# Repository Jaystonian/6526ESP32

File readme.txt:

6526ESP32

v0.1 - Largely disabled wifi, device boots into Ready mode instead of Modem mode
     - Added 1541diag (to use, poke 56704,5:poke 56705,0:sys56777)
     - Intended to use a new version of BASIC with new commands to use the
     device easily without pokes or sys calls, and also replace math etc.

v0.0 - straight conversion from ESP8266, added a few things but very dirty

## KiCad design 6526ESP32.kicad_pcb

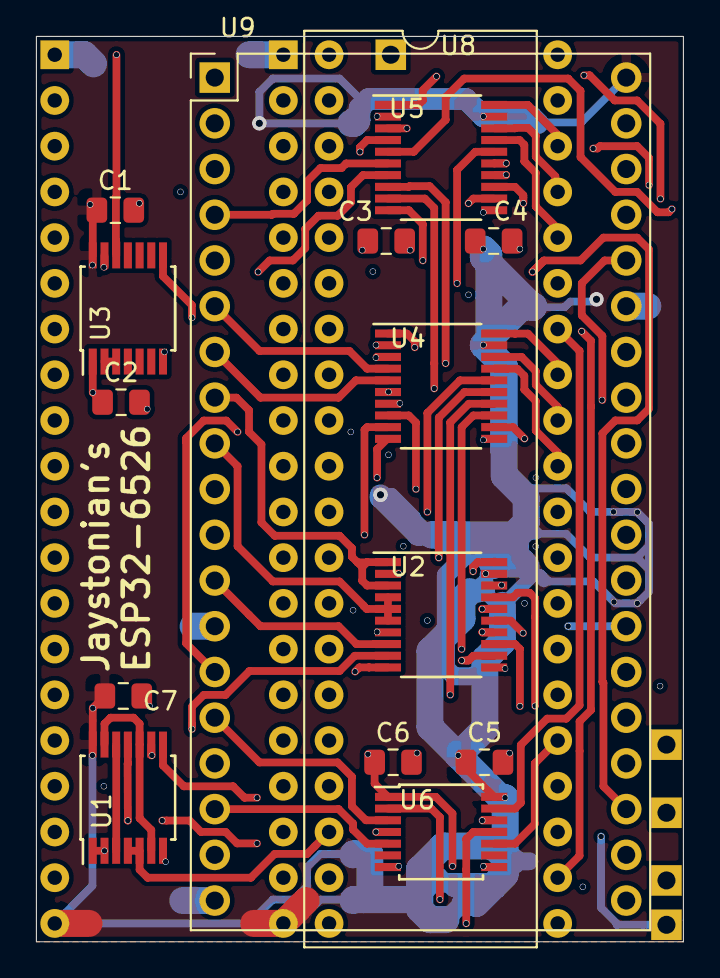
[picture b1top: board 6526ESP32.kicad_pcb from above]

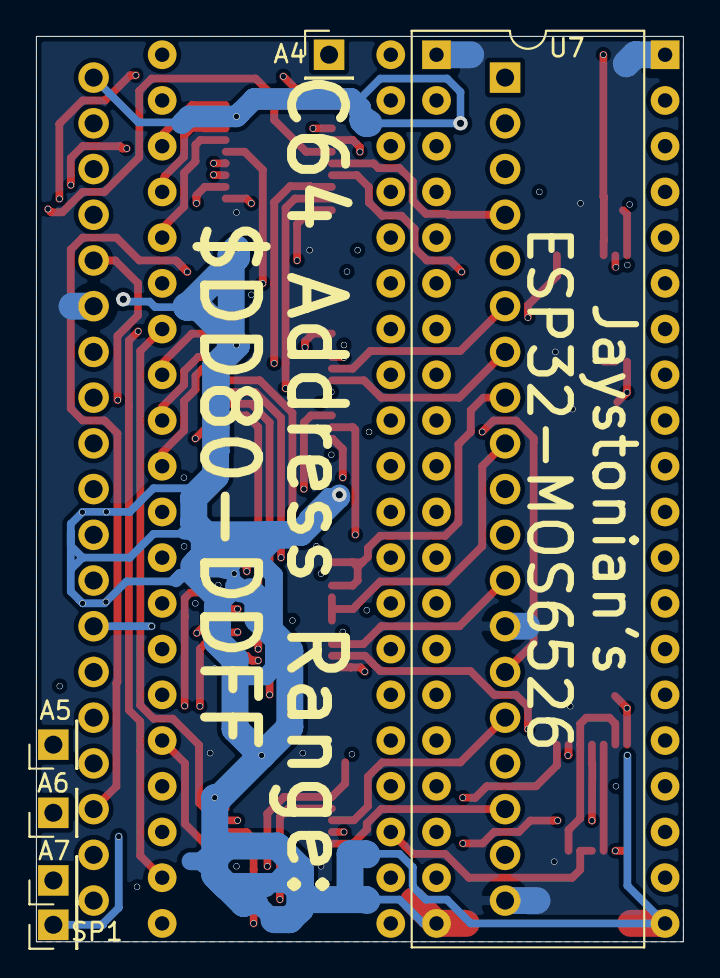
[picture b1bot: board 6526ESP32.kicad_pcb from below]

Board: 4 copper layers, 35.9 x 50.3 mm, 21 parts (5 on the bottom side), 78 nets.

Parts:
A4: A4; PinHeader_1x01_P2.54mm_Vertical
A5: A5; PinHeader_1x01_P2.54mm_Vertical
A6: A6; PinHeader_1x01_P2.54mm_Vertical
A7: A7; PinHeader_1x01_P2.54mm_Vertical
C1, C2, C3, C4, C5, C6, C7: 100n; C_0805_2012Metric_Pad1.15x1.40mm_HandSolder
SP1: SP1; PinHeader_1x01_P2.54mm_Vertical
U1: 74ABT00PW,112; TSSOP-14_4.4x5mm_P0.65mm
U2, U4, U5: TXS0108EQPWRQ1; TSSOP-20_4.4x6.5mm_P0.65mm
U3, U6: TXS0104EPW; TSSOP-14_4.4x5mm_P0.65mm
U7: MOS6526_SOCKET; DIP-40_W15.24mm
U8: MOS6526_CHIP; DIP-40_W15.24mm
U9: ESP32-DEVKIT-C; ESP32-DEV1

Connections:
+3V3: C2.1, C3.1, C6.1, U2.2, U3.1, U4.2, U5.2, U6.1, U6.8, U9.20
+5V: C1.1, C4.1, C5.1, C7.1, U1.14, U2.19, U3.14, U4.19, U5.19, U6.14, U7.20, U8.20, U9.38
/A0: U5.20, U7.38, U8.38
/A0_3V: U5.1, U9.24
/A1: U5.18, U7.37, U8.37
/A1_3V: U5.3, U9.25
/A2: U5.17, U7.36, U8.36
/A2_3V: U5.4, U9.22
/A3: U5.16, U7.35, U8.35
/A3_3V: U5.5, U9.23
/A4: A4.1, U5.15
/A4_3V: U5.6, U9.4
/A5: A5.1, U5.14
/A5_3V: U5.7, U9.10
/A6: A6.1, U5.13
/A6_3V: U5.8, U9.31
/A7: A7.1, U1.1, U1.2, U1.9
/CHIP~RESET: U6.13, U7.34, U8.34
/CHIP~RESET~3V: U6.2, U9.21
/CLK: U6.10, U7.25, U8.25
/CLK_3V: U6.5, U9.17
/CNT2: U3.12, U7.40, U8.40
/D0: U4.20, U7.33, U8.33
/D0_3V: U4.1, U9.27
/D1: U4.18, U7.32, U8.32
/D1_3V: U4.3, U9.14
/D2: U4.17, U7.31, U8.31
/D2_3V: U4.4, U9.6
/D3: U4.16, U7.30, U8.30
/D3_3V: U4.5, U9.7
/D4: U4.15, U7.29, U8.29
/D4_3V: U4.6, U9.30
/D5: U4.12, U7.28, U8.28
/D5_3V: U4.9, U9.28
/D6: U4.13, U7.27, U8.27
/D6_3V: U4.8, U9.29
/D7: U4.14, U7.26, U8.26
/D7_3V: U4.7, U9.34
/ENABLEMODEM_3V: U2.10, U3.8, U9.5
/GATE_ENABLE_3V: U4.10, U5.10, U9.32
/MODEM_CTS_3V: U2.8, U9.12
/MODEM_DCD_3V: U2.9, U9.18
/MODEM_RTS_3V: U2.7, U9.11
/MODEM_RXD_3V: U2.1, U2.3, U9.8
/MODEM_TXD_3V: U2.4, U2.5, U2.6, U9.9
/PA0: U7.2, U8.2
/PA1: U7.3, U8.3
/PA2: U2.20, U7.4, U8.4
/PA3: U7.5, U8.5
/PA4: U7.6, U8.6
/PA5: U7.7, U8.7
/PA6: U7.8, U8.8
/PA7: U7.9, U8.9
/PB0: U2.16, U7.10, U8.10
/PB1: U2.14, U7.11, U8.11
/PB2: U7.12, U8.12
/PB3: U7.13, U8.13
/PB4: U2.12, U7.14, U8.14
/PB5: U7.15, U8.15
/PB6: U2.13, U7.16, U8.16
/PB7: U3.13, U7.17, U8.17
/R~W: U5.12, U7.22, U8.22
/R~W~_3V: U5.9, U9.26
/SP1: SP1.1, U2.18
/SP2: U2.15, U7.39, U8.39
/TOD: U7.19, U8.19
/~CE: U1.4, U1.5, U7.23
/~CE6526: U1.11, U8.23
/~CHIPSELECT: U1.8, U6.12
/~CHIPSELECT3V: U6.3, U9.15
/~FLAG2: U2.17, U7.24, U8.24
/~NMI: U6.11, U7.21, U8.21
/~NMI_3V: U6.4, U9.16
/~PC: U7.18, U8.18
GND: C1.2, C2.2, C3.2, C4.2, C5.2, C6.2, C7.2, U1.7, U2.11, U3.7, U4.11, U5.11, U6.7, U7.1, U8.1, U9.13, U9.19, U9.33
unnamed: U1.6, U1.10, U1.13
unnamed: U1.3, U1.12
unnamed: U3.2, U3.3

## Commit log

2020-08-08 v0.0
